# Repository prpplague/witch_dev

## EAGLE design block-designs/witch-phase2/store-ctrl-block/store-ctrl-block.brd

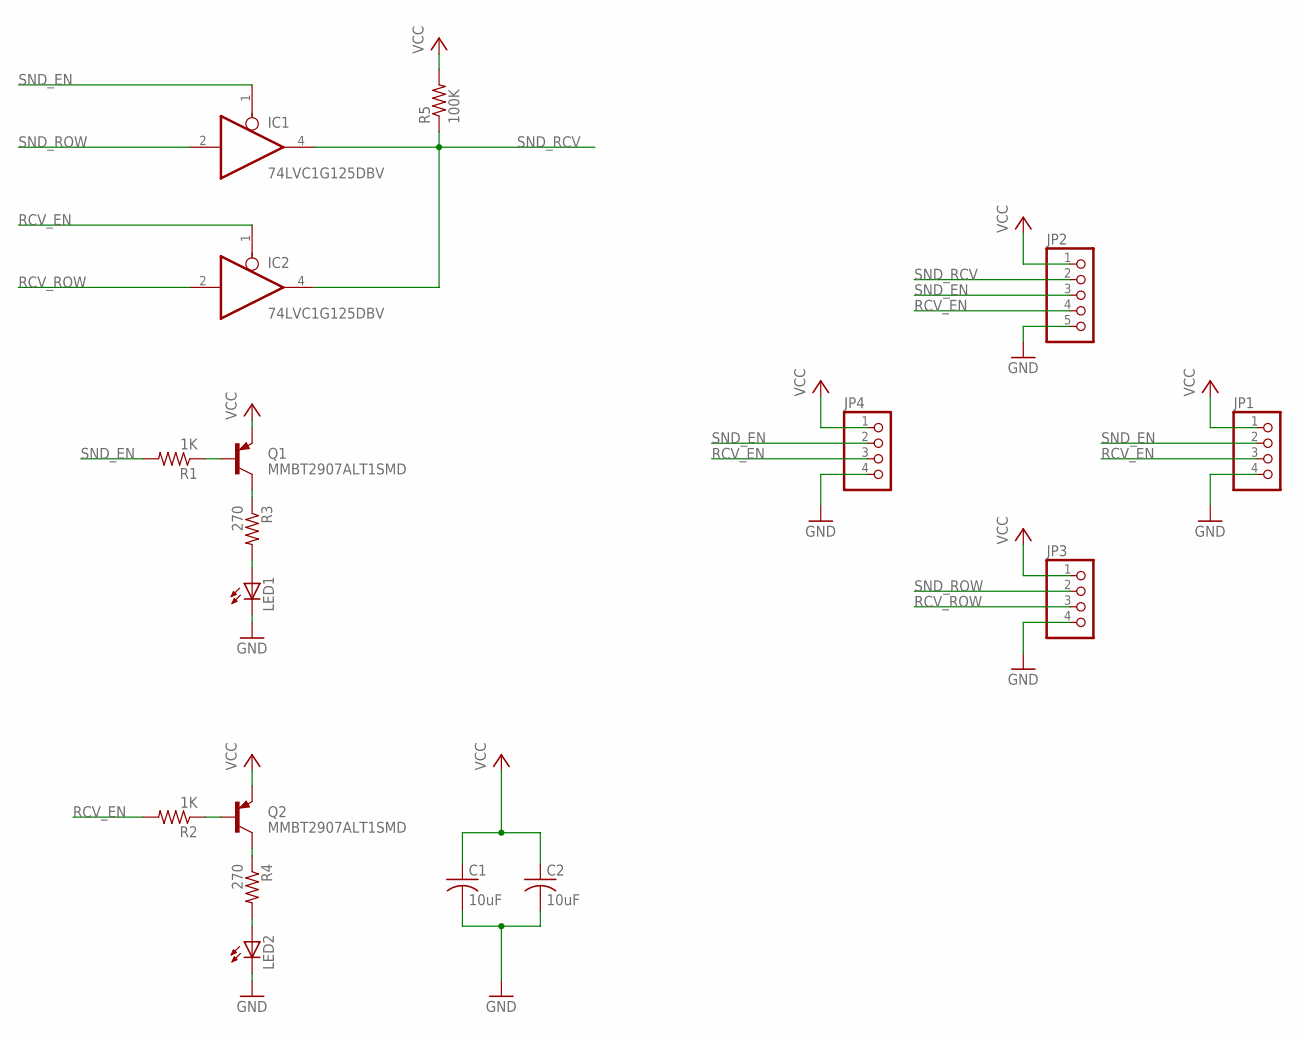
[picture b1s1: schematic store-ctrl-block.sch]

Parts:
C1, C2: 10uF; C0805
IC1, IC2: 74LVC1G125DBV; SOT23-5
JP1, JP3, JP4: PINHD-1X4; 1X04
JP2: PINHD-1X5; 1X05
LED1, LED2: LEDCHIP-LED0805; CHIP-LED0805
Q1, Q2: MMBT2907ALT1SMD; SOT23-BEC
R1, R2: 1K; R0805
R3, R4: 270; R0805
R5: 100K; R0805

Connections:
GND: C1.2, C2.2, IC1.3 (GND), IC2.3 (GND), JP1.4, JP2.5, JP3.4, JP4.4, LED1.C, LED2.C
unnamed: Q2.B, R2.1
unnamed: Q1.B, R1.1
unnamed: Q2.C, R4.1
unnamed: Q1.C, R3.1
unnamed: LED1.A, R3.2
unnamed: LED2.A, R4.2
RCV_EN: IC2.1 (OE), JP1.3, JP2.4, JP4.3, R2.2
RCV_ROW: IC2.2 (I), JP3.3
SND_EN: IC1.1 (OE), JP1.2, JP2.3, JP4.2, R1.2
SND_RCV: IC1.4 (O), IC2.4 (O), JP2.2, R5.1
SND_ROW: IC1.2 (I), JP3.2
VCC: C1.1, C2.1, IC1.5 (VCC), IC2.5 (VCC), JP1.1, JP2.1, JP3.1, JP4.1, Q1.E, Q2.E, R5.2

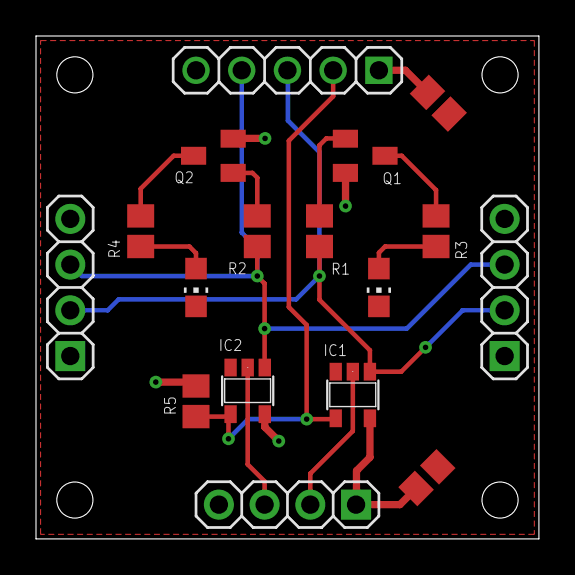
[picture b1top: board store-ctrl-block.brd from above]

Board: 2 copper layers, 27.9 x 27.9 mm, 17 parts (0 on the bottom side), 13 nets.

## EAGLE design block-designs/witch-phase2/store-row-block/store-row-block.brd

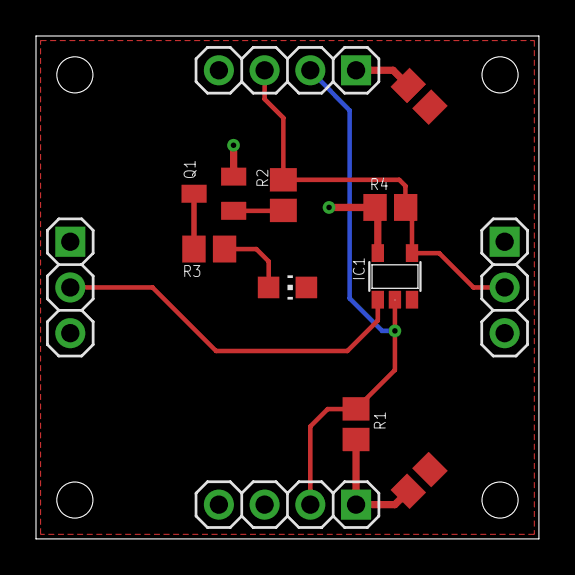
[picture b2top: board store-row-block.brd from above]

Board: 2 copper layers, 27.9 x 27.9 mm, 13 parts (0 on the bottom side), 8 nets.

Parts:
C1, C4: C0805
IC1: 74LVC1G125DBV; SOT23-5
JP1, JP3: 1X03
JP2, JP4: 1X04
LED1: CHIP-LED0805
Q1: MMBT2907ALT1SMD; SOT23-BEC
R1, R2, R3, R4: R0805

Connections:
ENABLE: IC1.1, JP1.2
GND: C1.2, C4.2, IC1.3, JP1.3, JP2.4, JP3.3, JP4.4, LED1.C
unnamed: Q1.B, R2.1
unnamed: Q1.C, R3.1
unnamed: LED1.A, R3.2
ROW_EN: IC1.4, JP2.3, JP3.2, R2.2, R4.1
SND_RCV: IC1.2, JP2.2, JP4.2, R1.1
VCC: C1.1, C4.1, IC1.5, JP2.1, JP4.1, Q1.E, R1.2, R4.2

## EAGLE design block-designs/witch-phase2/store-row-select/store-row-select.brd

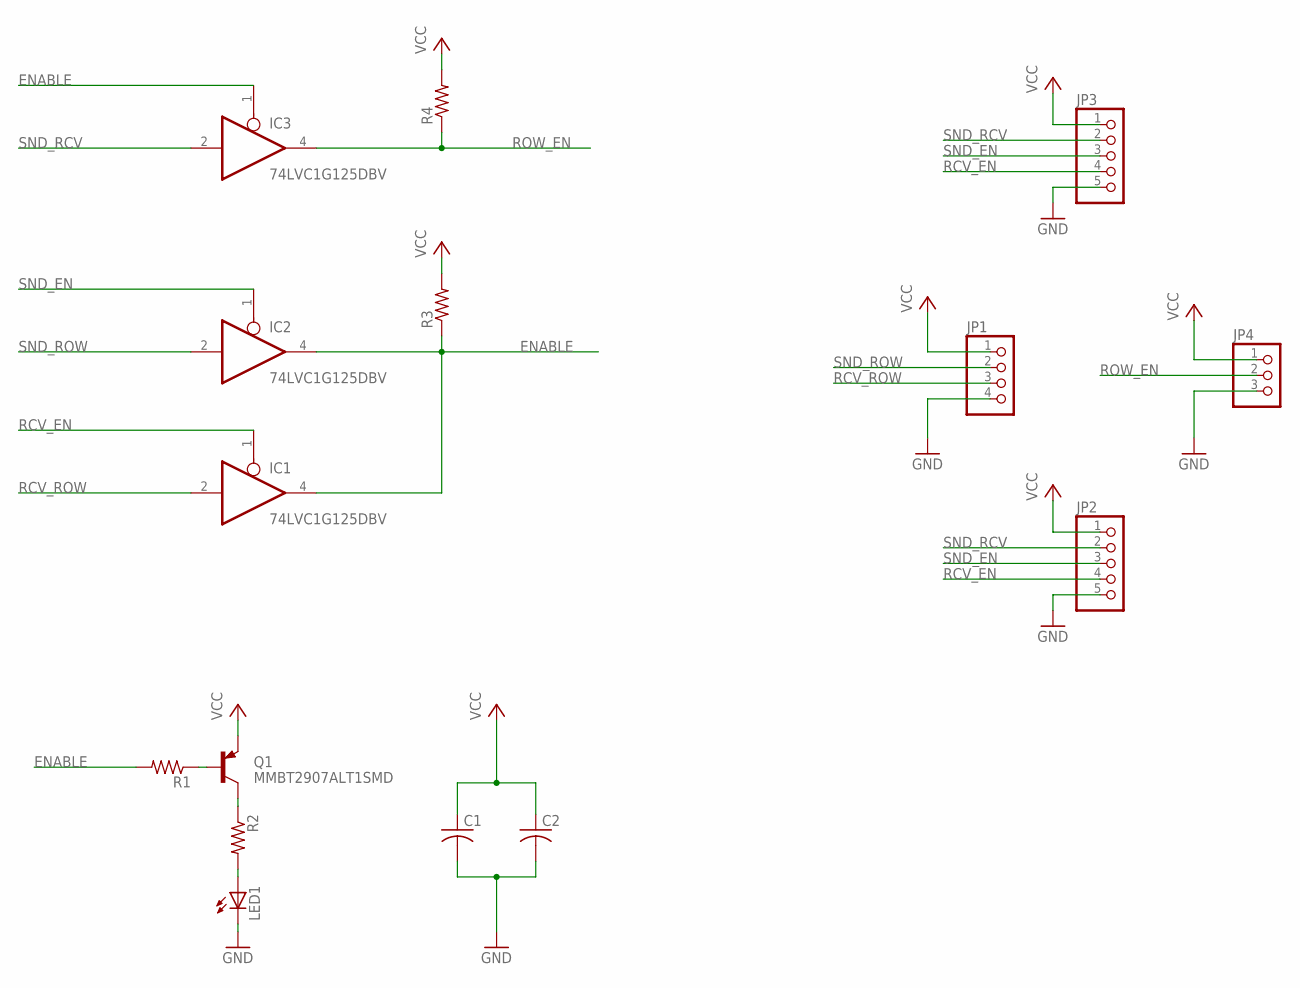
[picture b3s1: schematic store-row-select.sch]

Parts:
C1, C2: C-USC0805; C0805
IC1, IC2, IC3: 74LVC1G125DBV; SOT23-5
JP1: PINHD-1X4; 1X04
JP2, JP3: PINHD-1X5; 1X05
JP4: PINHD-1X3; 1X03
LED1: LEDCHIP-LED0805; CHIP-LED0805
Q1: MMBT2907ALT1SMD; SOT23-BEC
R1, R2, R3, R4: R-US_R0805; R0805

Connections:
ENABLE: IC1.4 (O), IC2.4 (O), IC3.1 (OE), R1.2, R3.1
GND: C1.2, C2.2, IC1.3 (GND), IC2.3 (GND), IC3.3 (GND), JP1.4, JP2.5, JP3.5, JP4.3, LED1.C
unnamed: Q1.B, R1.1
unnamed: Q1.C, R2.1
unnamed: LED1.A, R2.2
RCV_EN: IC1.1 (OE), JP2.4, JP3.4
RCV_ROW: IC1.2 (I), JP1.3
ROW_EN: IC3.4 (O), JP4.2, R4.1
SND_EN: IC2.1 (OE), JP2.3, JP3.3
SND_RCV: IC3.2 (I), JP2.2, JP3.2
SND_ROW: IC2.2 (I), JP1.2
VCC: C1.1, C2.1, IC1.5 (VCC), IC2.5 (VCC), IC3.5 (VCC), JP1.1, JP2.1, JP3.1, JP4.1, Q1.E, R3.2, R4.2

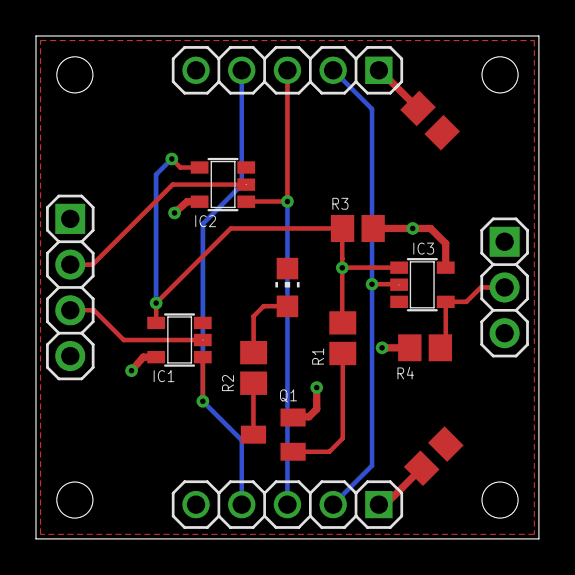
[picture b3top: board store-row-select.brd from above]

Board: 2 copper layers, 27.9 x 27.9 mm, 15 parts (0 on the bottom side), 12 nets.

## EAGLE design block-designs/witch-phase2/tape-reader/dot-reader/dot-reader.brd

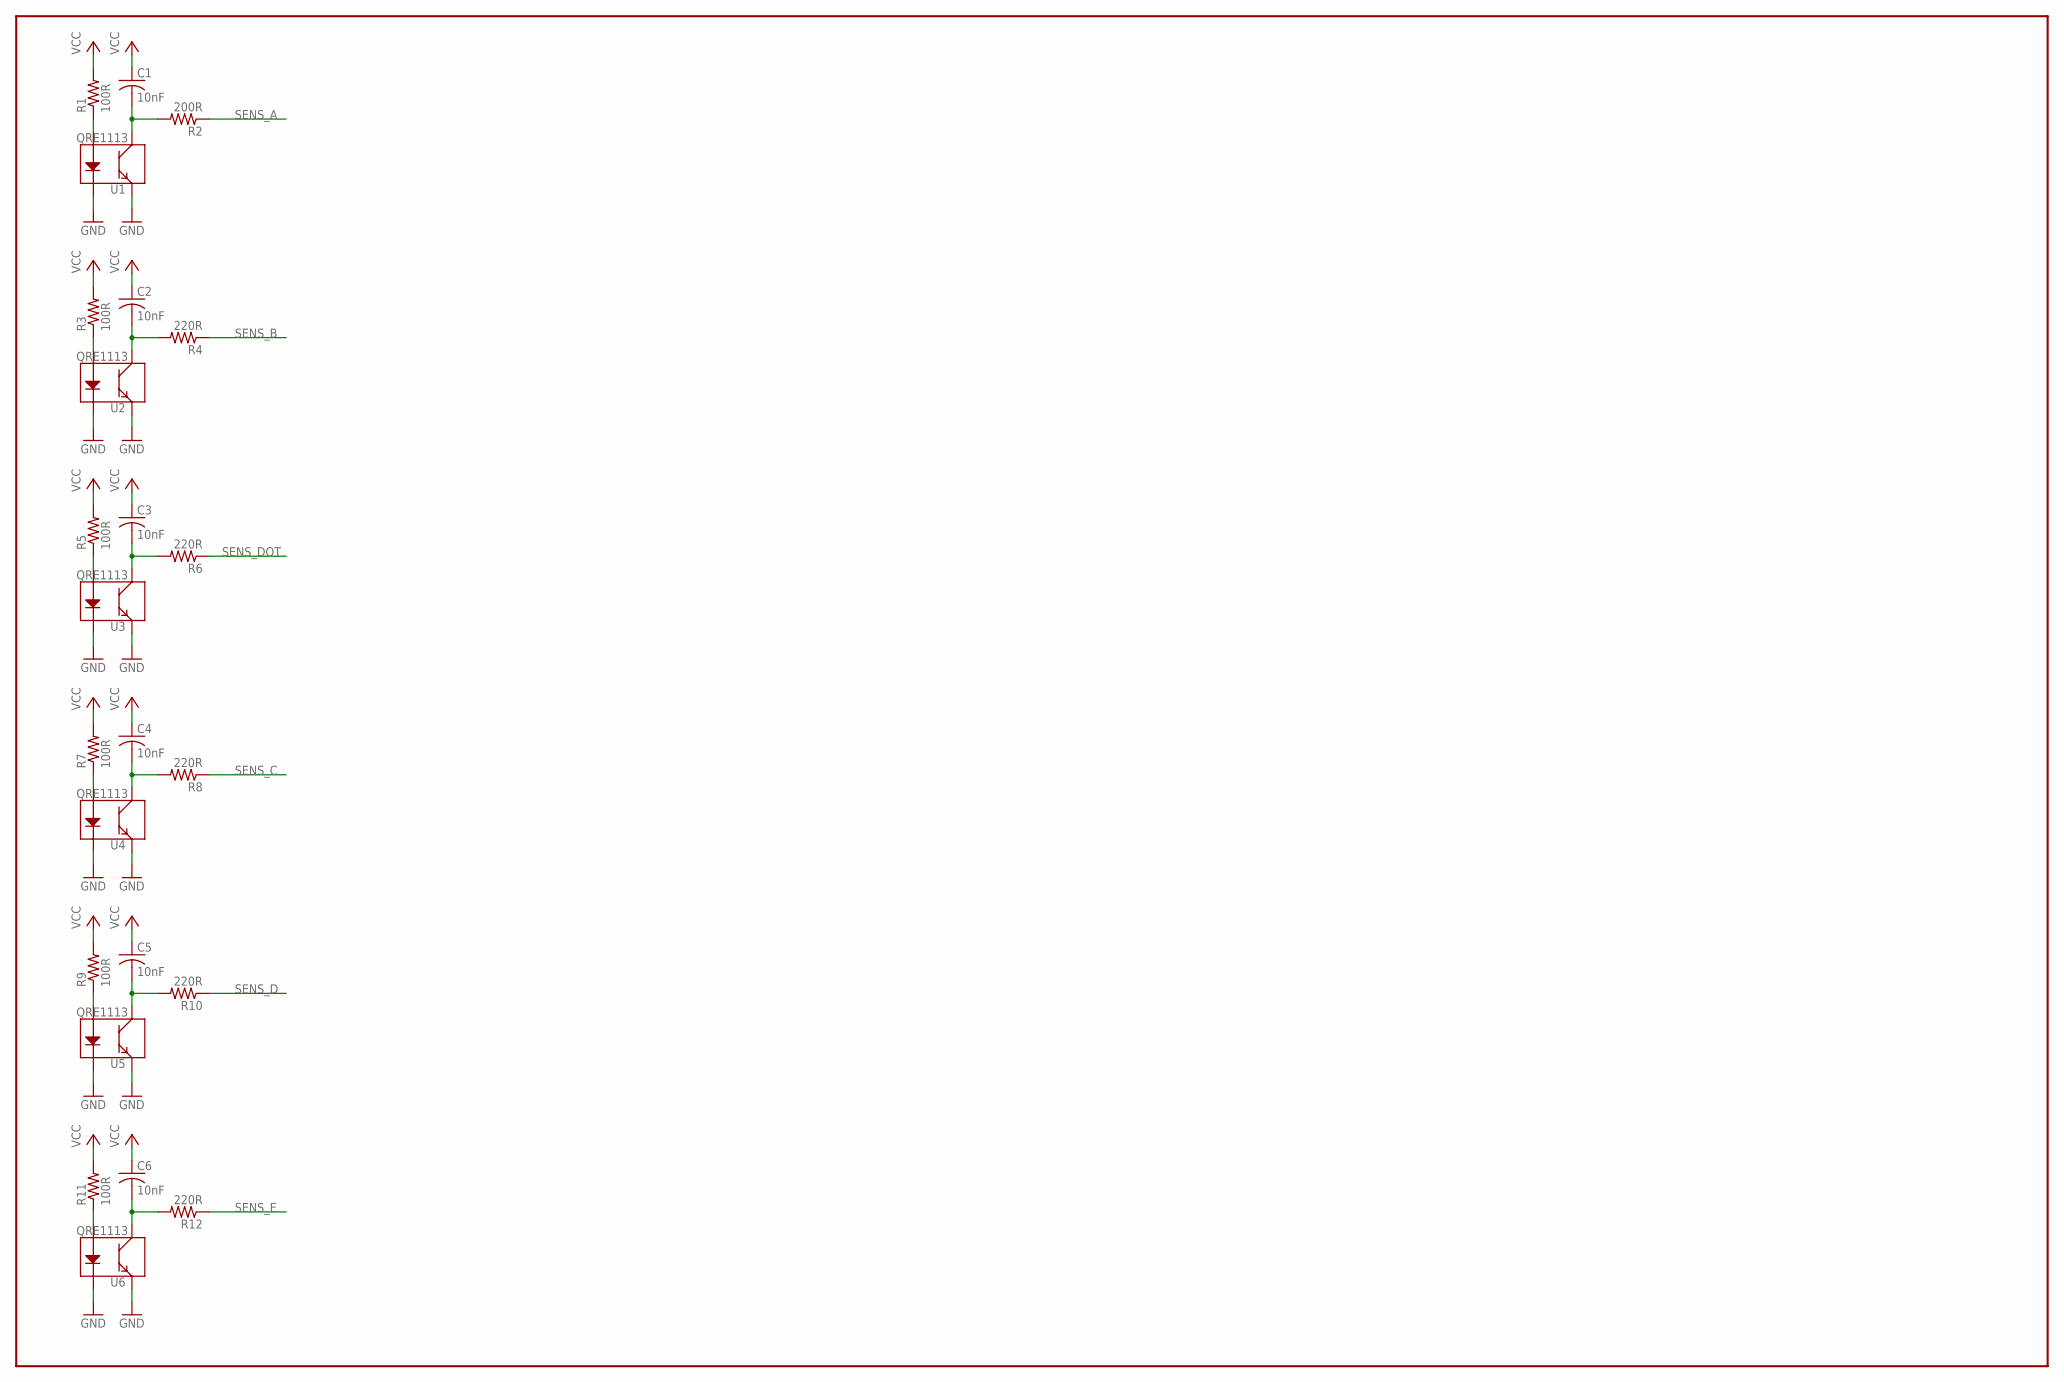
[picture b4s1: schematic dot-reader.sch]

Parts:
C1, C2, C3, C4, C5, C6: 10nF; C0805
R1, R3, R5, R7, R9, R11: 100R; M0805
R2: 200R; M0805
R4, R6, R8, R10, R12: 220R; M0805
U1, U2, U3, U4, U5, U6: QRE1113

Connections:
GND: U1.2 (K), U1.4 (E), U2.2 (K), U2.4 (E), U3.2 (K), U3.4 (E), U4.2 (K), U4.4 (E), U5.2 (K), U5.4 (E), U6.2 (K), U6.4 (E)
unnamed: R1.1, U1.1 (A)
unnamed: C1.2, R2.2, U1.3 (C)
unnamed: R3.1, U2.1 (A)
unnamed: C2.2, R4.2, U2.3 (C)
unnamed: R5.1, U3.1 (A)
unnamed: C3.2, R6.2, U3.3 (C)
unnamed: R7.1, U4.1 (A)
unnamed: C4.2, R8.2, U4.3 (C)
unnamed: R9.1, U5.1 (A)
unnamed: C5.2, R10.2, U5.3 (C)
unnamed: R11.1, U6.1 (A)
unnamed: C6.2, R12.2, U6.3 (C)
SENS_A: R2.1
SENS_B: R4.1
SENS_C: R8.1
SENS_D: R10.1
SENS_DOT: R6.1
SENS_E: R12.1
VCC: C1.1, C2.1, C3.1, C4.1, C5.1, C6.1, R1.2, R3.2, R5.2, R7.2, R9.2, R11.2

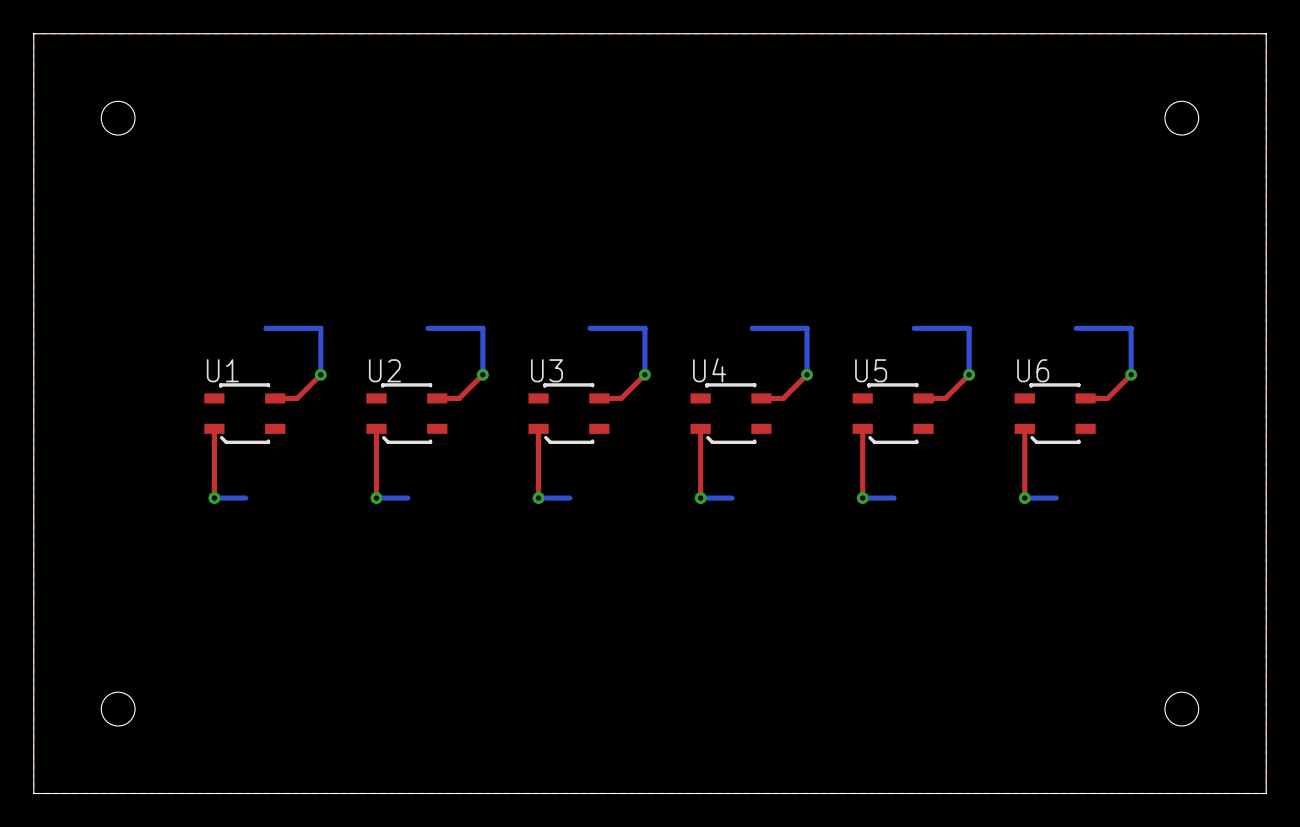
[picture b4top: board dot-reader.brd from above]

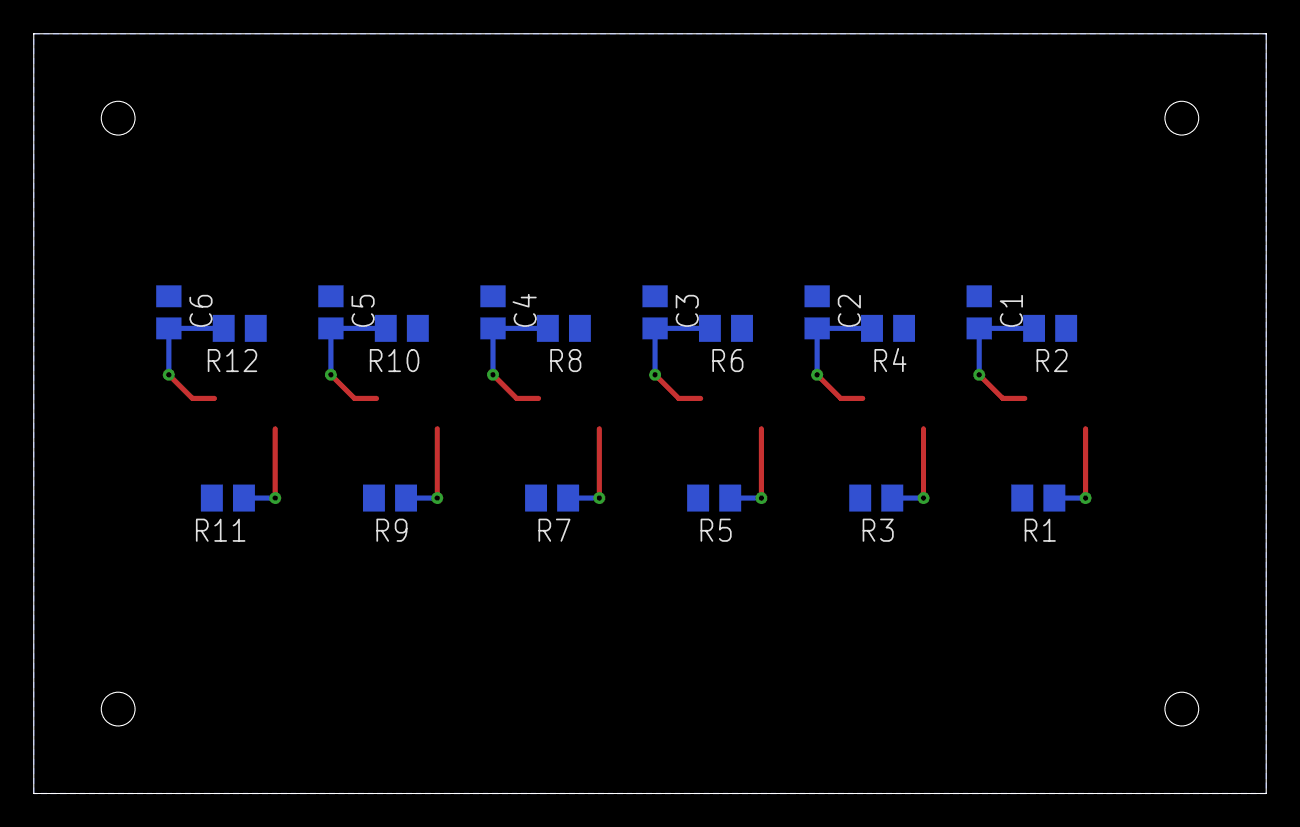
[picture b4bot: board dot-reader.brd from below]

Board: 2 copper layers, 73.0 x 45.0 mm, 24 parts (18 on the bottom side), 14 nets.

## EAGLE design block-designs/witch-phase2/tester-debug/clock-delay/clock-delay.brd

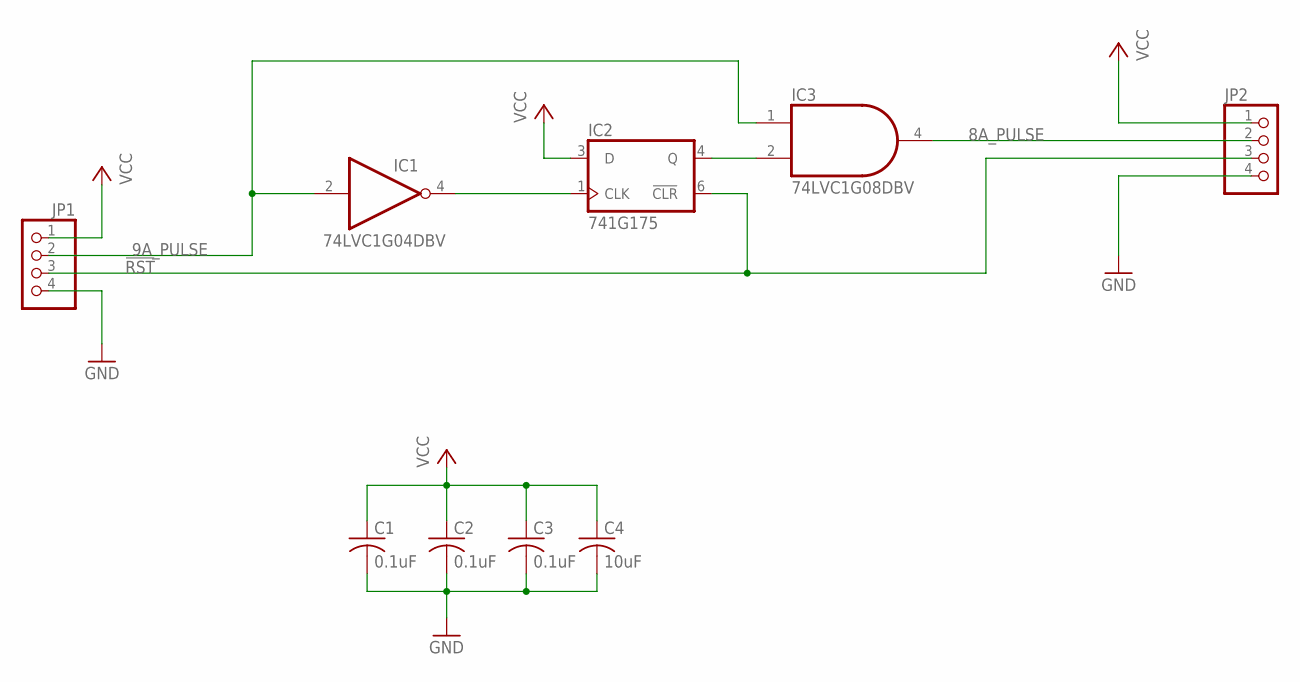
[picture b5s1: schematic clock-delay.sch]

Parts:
C1, C2, C3: 0.1uF; C0805
C4: 10uF; C0805
IC1: 74LVC1G04DBV; SOT23-5
IC2: 741G175; DBV_R-PDSO-G6
IC3: 74LVC1G08DBV; SOT23-5
JP1, JP2: PINHD-1X4; 1X04

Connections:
8A_PULSE: IC3.4 (O), JP2.2
9A_PULSE: IC1.2 (I), IC3.1 (I0), JP1.2
!RST: IC2.6 (!CLR), JP1.3, JP2.3
GND: C1.2, C2.2, C3.2, C4.2, IC1.3 (GND), IC2.2 (GND), IC3.3 (GND), JP1.4, JP2.4
unnamed: IC2.4 (Q), IC3.2 (I1)
unnamed: IC1.4 (O), IC2.1 (CLK)
VCC: C1.1, C2.1, C3.1, C4.1, IC1.5 (VCC), IC2.3 (D), IC2.5 (VCC), IC3.5 (VCC), JP1.1, JP2.1

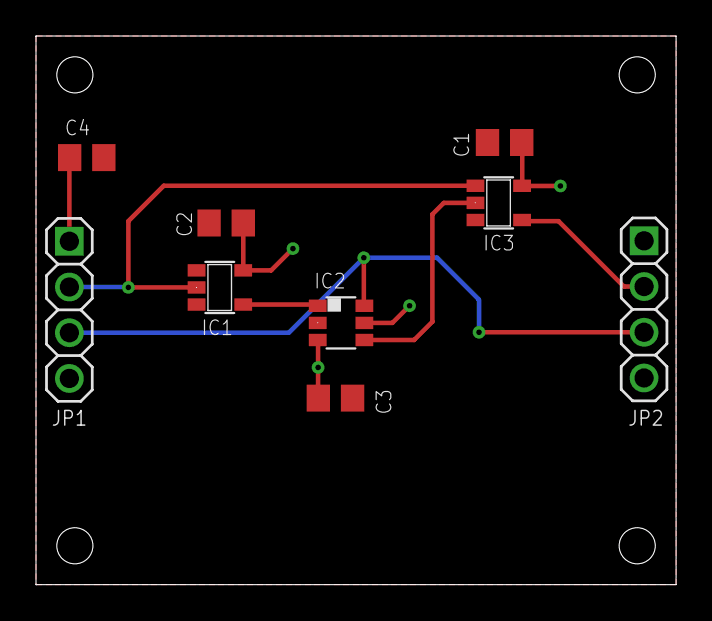
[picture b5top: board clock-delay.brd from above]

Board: 2 copper layers, 35.6 x 30.5 mm, 9 parts (0 on the bottom side), 7 nets.

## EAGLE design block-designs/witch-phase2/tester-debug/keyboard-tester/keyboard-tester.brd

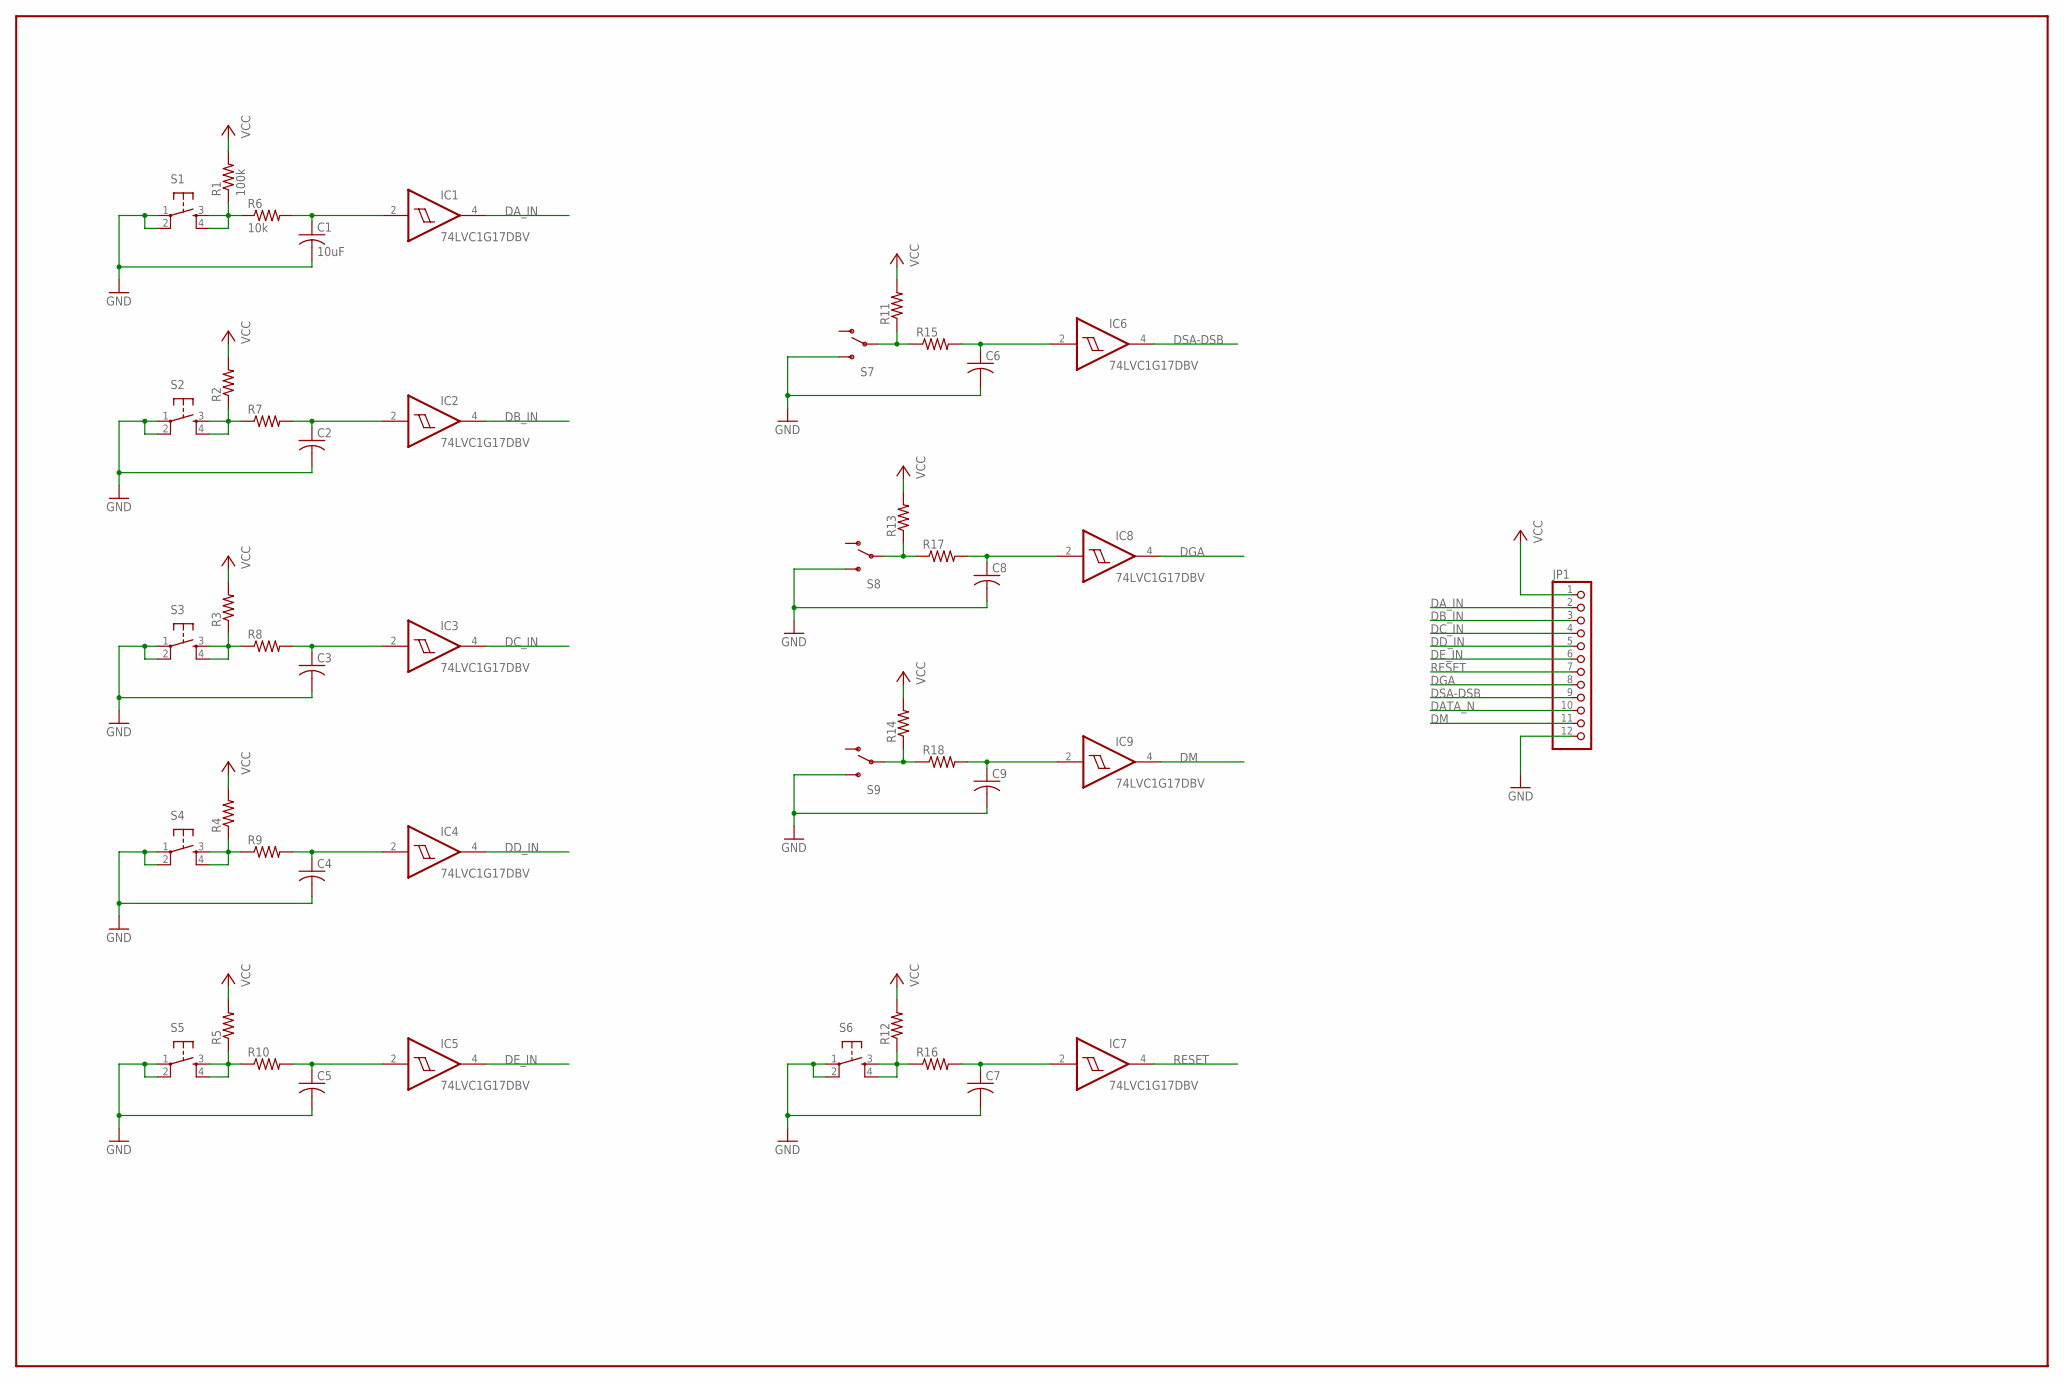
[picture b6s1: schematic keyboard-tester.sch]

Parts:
C1: 10uF; C0805
C2, C3, C4, C5, C6, C7, C8, C9: C-USC0805; C0805
IC1, IC2, IC3, IC4, IC5, IC6, IC7, IC8, IC9: 74LVC1G17DBV; SOT23-5
JP1: PINHD-1X12; 1X12
R1: 100k; R0805
R2, R3, R4, R5, R7, R8, R9, R10, R11, R12, R13, R14, R15, R16, R17, R18: R-US_R0805; R0805
R6: 10k; R0805
S1, S2, S3, S4, S5, S6: TAC_SWITCHPTH; TACTILE-PTH
S7, S8, S9: SWITCH-SPDTPTH; SWITCH-SPDT

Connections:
DATA_N: JP1.10
DA_IN: IC1.4 (O), JP1.2
DB_IN: IC2.4 (O), JP1.3
DC_IN: IC3.4 (O), JP1.4
DD_IN: IC4.4 (O), JP1.5
DE_IN: IC5.4 (O), JP1.6
DGA: IC8.4 (O), JP1.8
DM: IC9.4 (O), JP1.11
DSA-DSB: IC6.4 (O), JP1.9
GND: C1.2, C2.2, C3.2, C4.2, C5.2, C6.2, C7.2, C8.2, C9.2, IC1.3 (GND), IC2.3 (GND), IC3.3 (GND), IC4.3 (GND), IC5.3 (GND), IC6.3 (GND), IC7.3 (GND), IC8.3 (GND), IC9.3 (GND), JP1.12, S1.1, S1.2, S2.1, S2.2, S3.1, S3.2, S4.1, S4.2, S5.1, S5.2, S6.1, S6.2, S7.3 (S), S8.3 (S), S9.3 (S)
unnamed: R1.1, R6.1, S1.3, S1.4
unnamed: C1.1, IC1.2 (I), R6.2
unnamed: C2.1, IC2.2 (I), R7.2
unnamed: R2.1, R7.1, S2.3, S2.4
unnamed: C3.1, IC3.2 (I), R8.2
unnamed: R3.1, R8.1, S3.3, S3.4
unnamed: C4.1, IC4.2 (I), R9.2
unnamed: R4.1, R9.1, S4.3, S4.4
unnamed: C5.1, IC5.2 (I), R10.2
unnamed: R5.1, R10.1, S5.3, S5.4
unnamed: C7.1, IC7.2 (I), R16.2
unnamed: R12.1, R16.1, S6.3, S6.4
unnamed: C6.1, IC6.2 (I), R15.2
unnamed: R11.1, R15.1, S7.2
unnamed: C8.1, IC8.2 (I), R17.2
unnamed: R13.1, R17.1, S8.2
unnamed: C9.1, IC9.2 (I), R18.2
unnamed: R14.1, R18.1, S9.2
RESET: IC7.4 (O), JP1.7
VCC: IC1.5 (VCC), IC2.5 (VCC), IC3.5 (VCC), IC4.5 (VCC), IC5.5 (VCC), IC6.5 (VCC), IC7.5 (VCC), IC8.5 (VCC), IC9.5 (VCC), JP1.1, R1.2, R2.2, R3.2, R4.2, R5.2, R11.2, R12.2, R13.2, R14.2

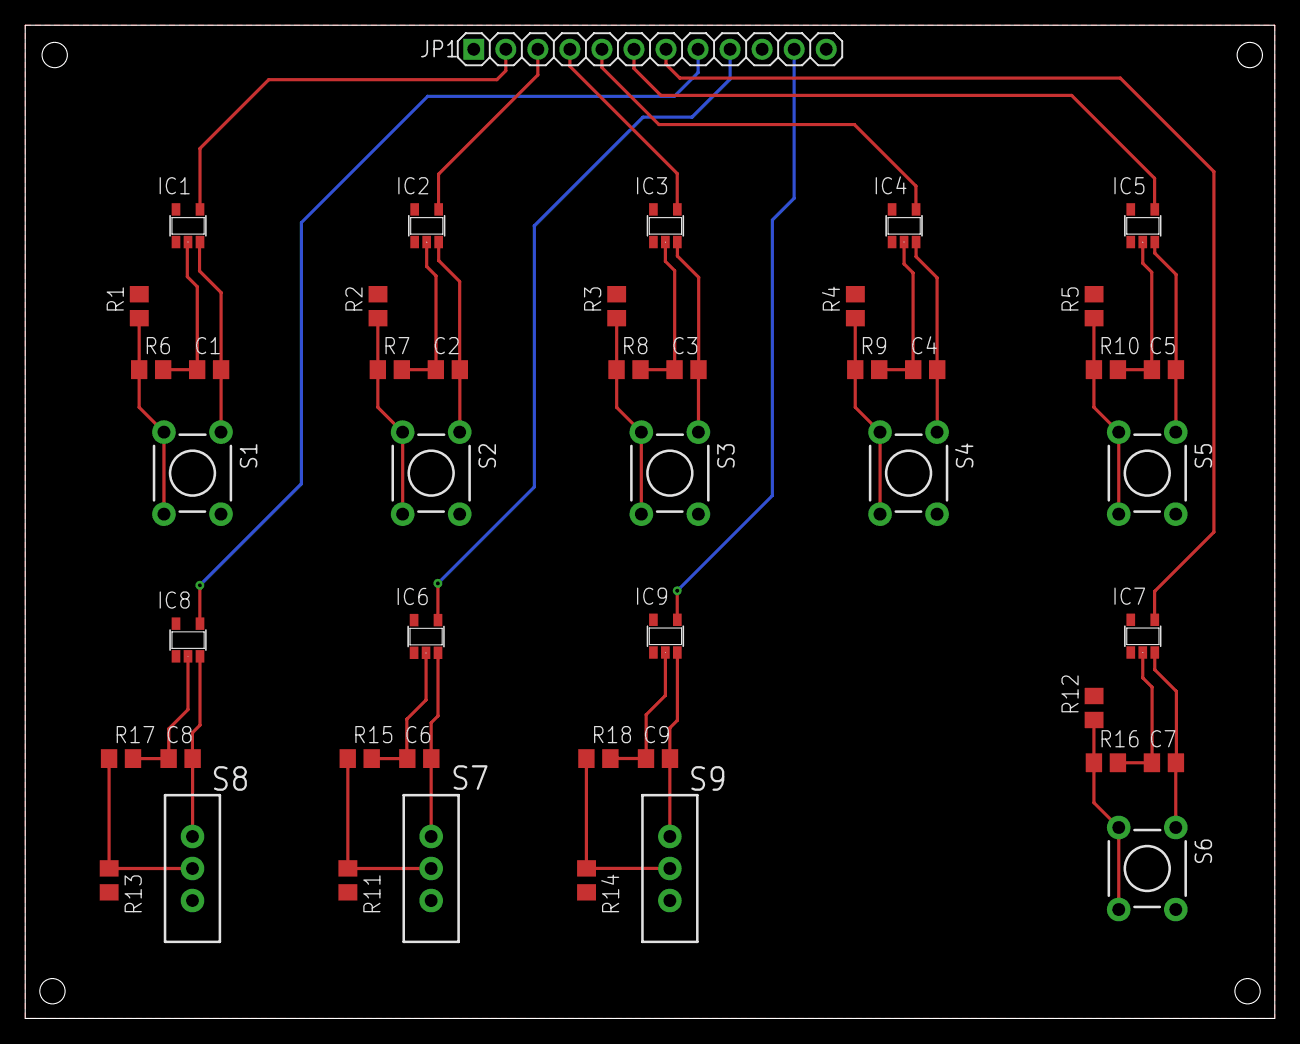
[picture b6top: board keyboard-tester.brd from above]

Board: 2 copper layers, 99.1 x 78.7 mm, 46 parts (0 on the bottom side), 29 nets.

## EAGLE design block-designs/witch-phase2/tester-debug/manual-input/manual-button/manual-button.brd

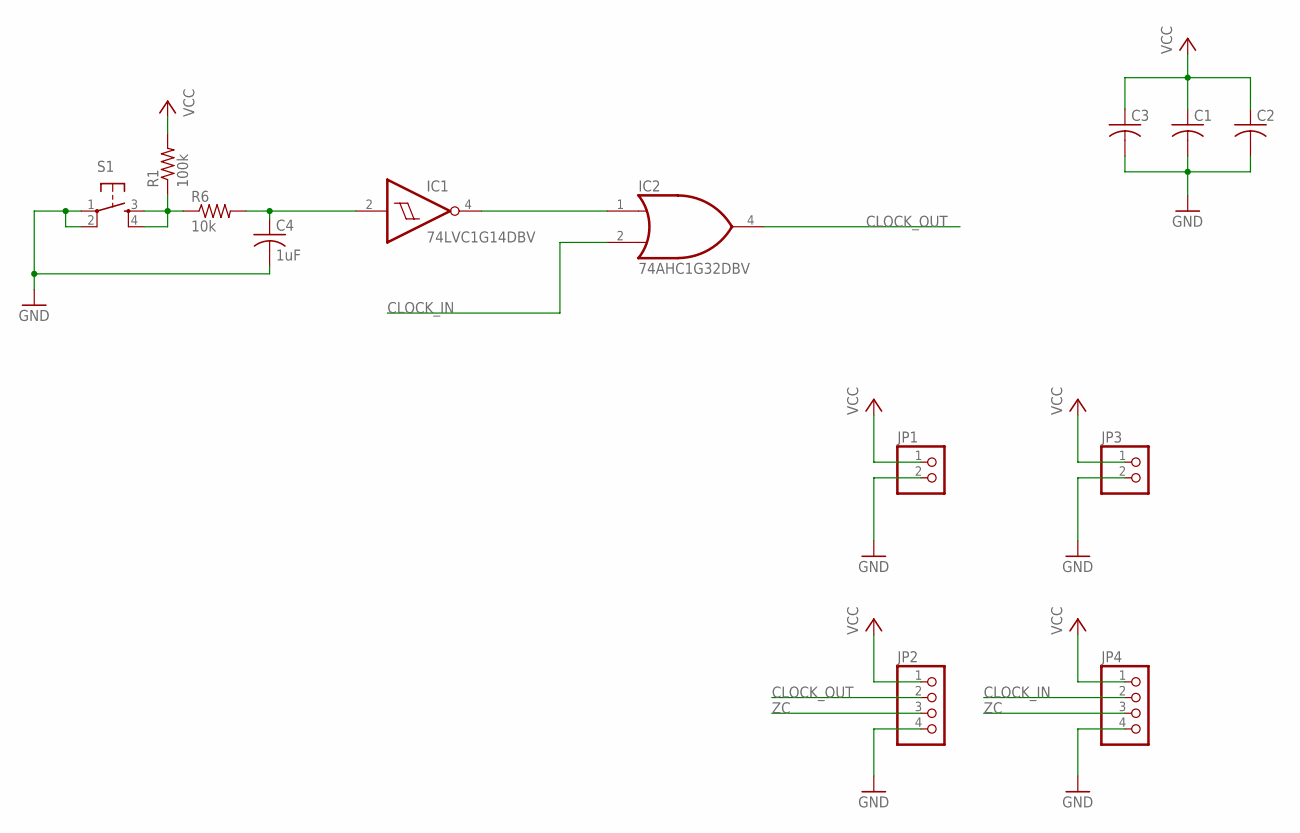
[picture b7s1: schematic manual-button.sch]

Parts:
C1, C2, C3: C-USC0603K; C0603K
C4: 1uF; C0603K
IC1: 74LVC1G14DBV; SOT23-5
IC2: 74AHC1G32DBV; SOT23-5
JP1, JP3: PINHD-1X2; 1X02
JP2, JP4: PINHD-1X4; 1X04
R1: 100k; R0603
R6: 10k; R0603
S1: TAC_SWITCHPTH; TACTILE-PTH

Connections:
CLOCK_IN: IC2.2 (I1), JP4.2
CLOCK_OUT: IC2.4 (O), JP2.2
DA_IN: IC1.4 (O), IC2.1 (I0)
GND: C1.2, C2.2, C3.2, C4.2, IC1.3 (GND), IC2.3 (GND), JP1.2, JP2.4, JP3.2, JP4.4, S1.1, S1.2
unnamed: R1.1, R6.1, S1.3, S1.4
unnamed: C4.1, IC1.2 (I), R6.2
VCC: C1.1, C2.1, C3.1, IC1.5 (VCC), IC2.5 (VCC), JP1.1, JP2.1, JP3.1, JP4.1, R1.2
ZC: JP2.3, JP4.3

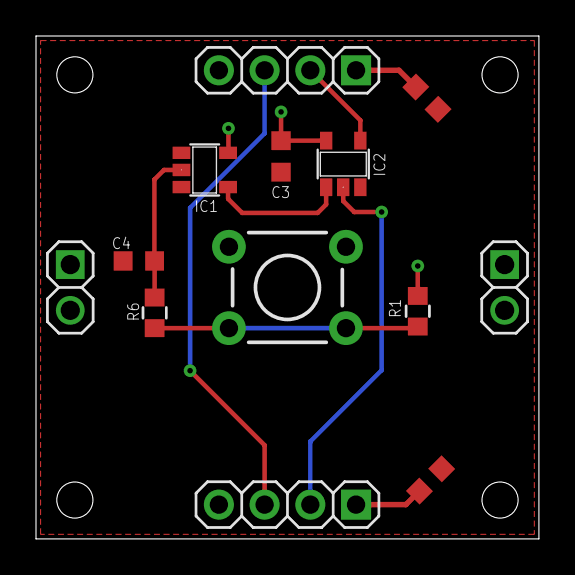
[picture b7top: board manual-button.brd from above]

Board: 2 copper layers, 27.9 x 27.9 mm, 13 parts (0 on the bottom side), 8 nets.

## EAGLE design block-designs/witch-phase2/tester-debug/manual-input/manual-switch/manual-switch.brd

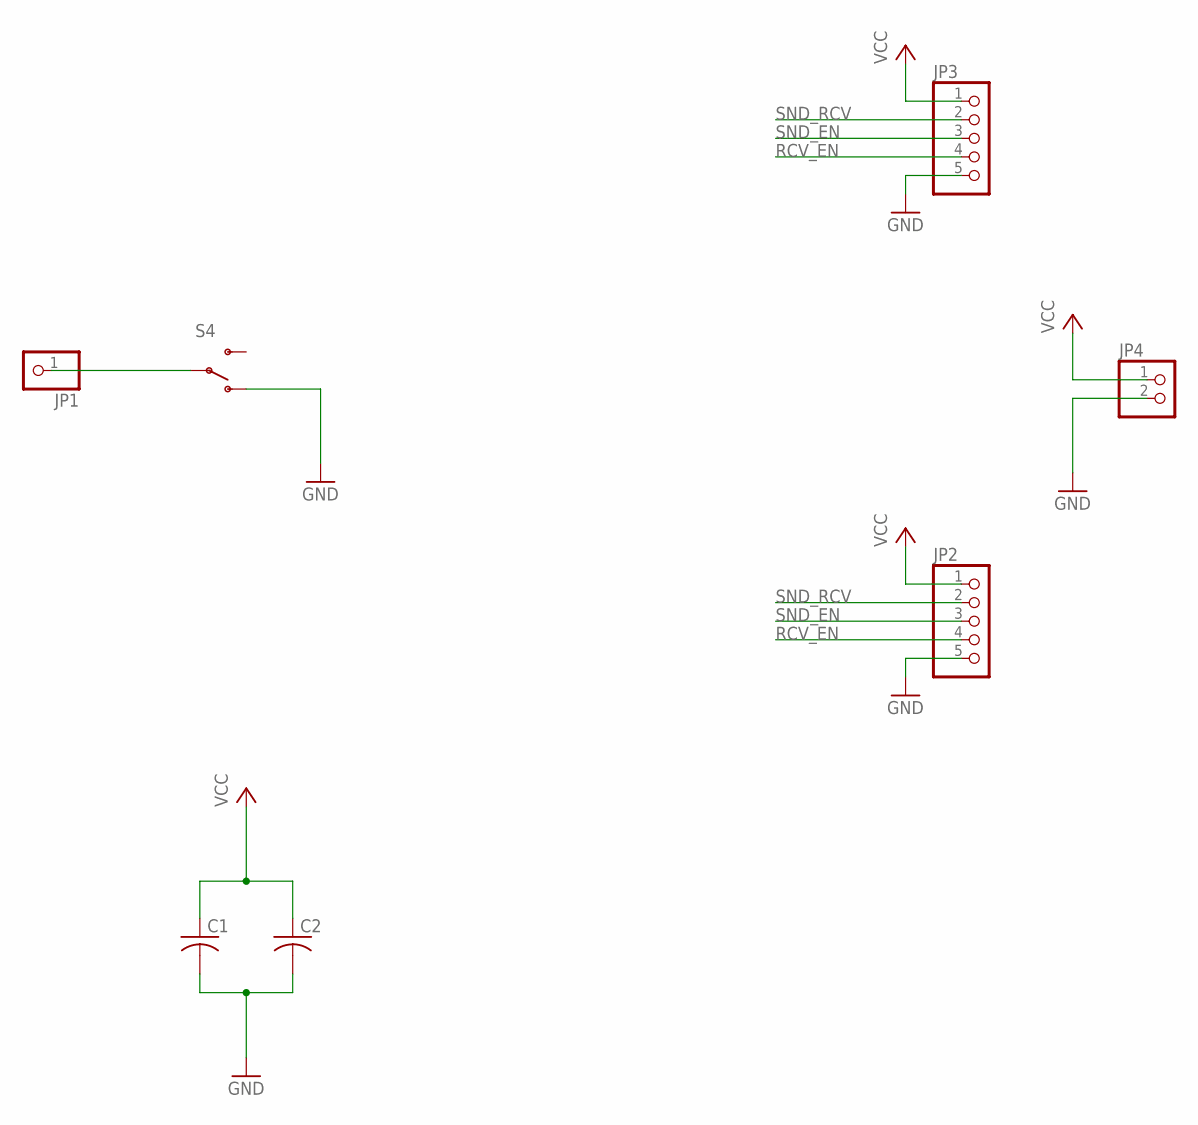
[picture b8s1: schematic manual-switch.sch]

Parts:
C1, C2: C-USC0805; C0805
JP1: PINHD-1X1; 1X01
JP2, JP3: PINHD-1X5; 1X05
JP4: PINHD-1X2; 1X02
S4: SWITCH-SPDTPTH; SWITCH-SPDT

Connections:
GND: C1.2, C2.2, JP2.5, JP3.5, JP4.2, S4.1 (O)
unnamed: JP1.1, S4.2
RCV_EN: JP2.4, JP3.4
SND_EN: JP2.3, JP3.3
SND_RCV: JP2.2, JP3.2
VCC: C1.1, C2.1, JP2.1, JP3.1, JP4.1

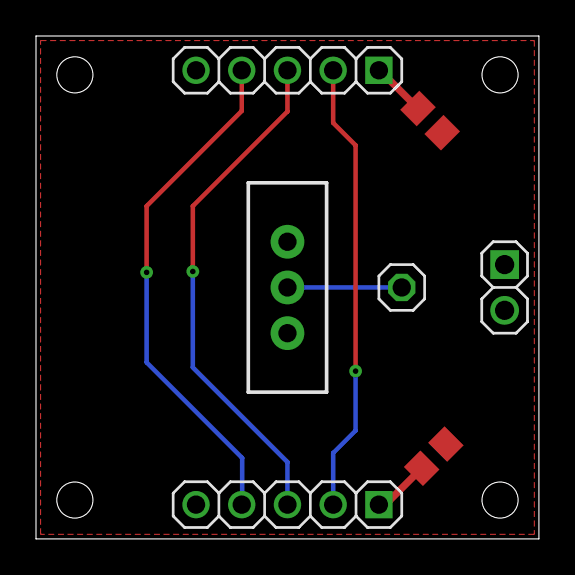
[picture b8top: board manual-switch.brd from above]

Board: 2 copper layers, 27.9 x 27.9 mm, 7 parts (0 on the bottom side), 6 nets.

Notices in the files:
parts and their libraries:
SparkFun-Electromechanical: Licensing: CC v3.0 Share-Alike You are welcome to use this library for commercial purposes.
SparkFun-Sensors: Licensing: Creative Commons ShareAlike 4.0 International - https://creativecommons.org/licenses/by-sa/4.0
